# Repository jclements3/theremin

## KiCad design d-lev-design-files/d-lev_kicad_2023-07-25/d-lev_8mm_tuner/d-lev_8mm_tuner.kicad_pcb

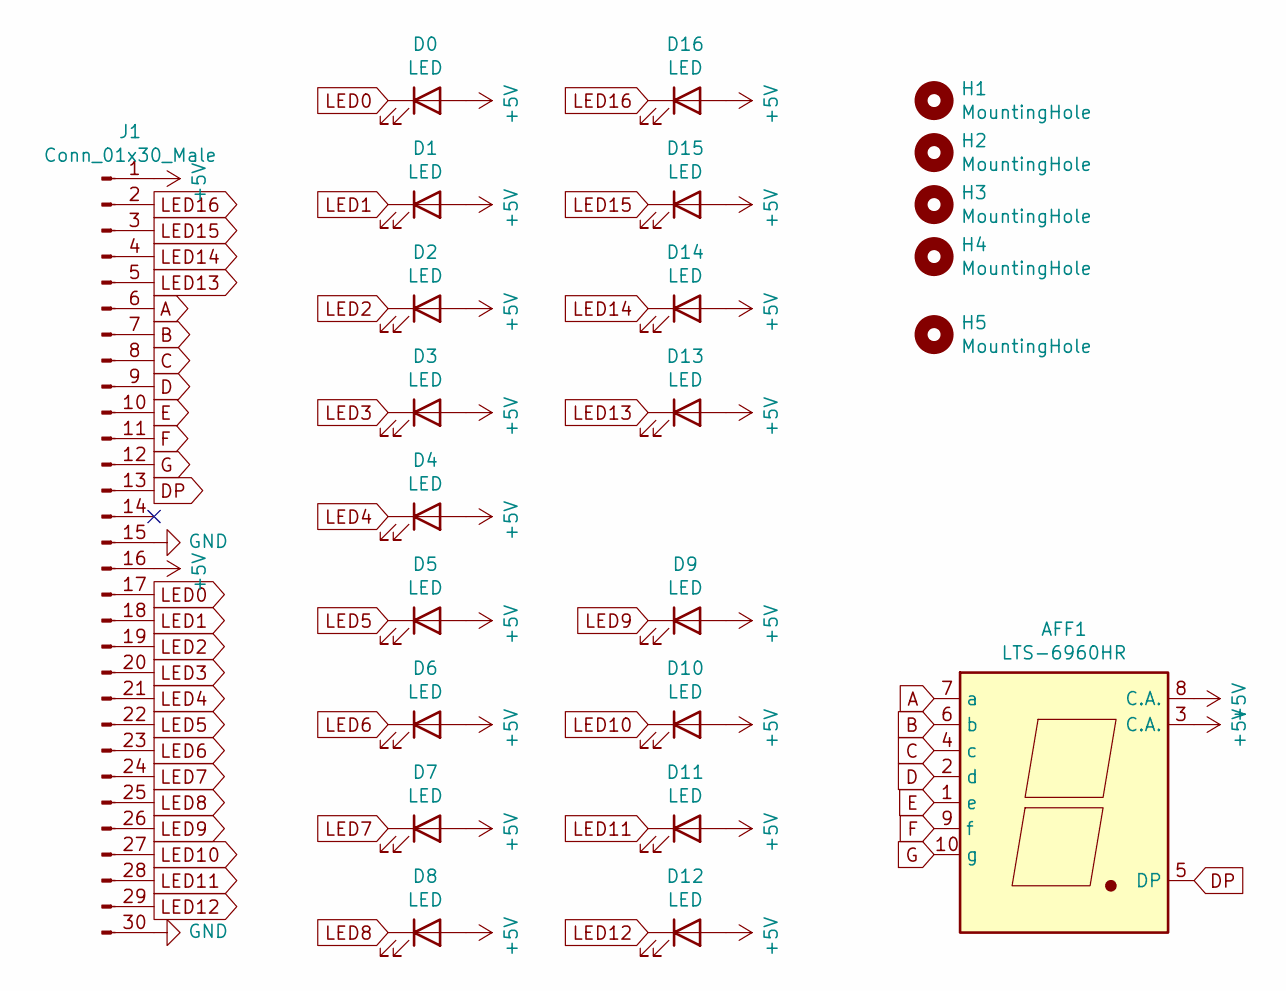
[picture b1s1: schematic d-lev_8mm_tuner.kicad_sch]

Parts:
AFF1: LTS-6960HR; 7-segment_half_inch
D0, D1, D2, D3, D4, D5, D6, D7, D8, D9, D10, D11, D12, D13, D14, D15, D16: LED; LED_D8.0mm
H1, H2, H3, H4: MountingHole; MountingHole_3.2mm_M3
H5: MountingHole; MountingHole_2.5mm_Pad_TopBottom
J1: Conn_01x30_Male; PinHeader_1x30_P2.54mm_Vertical

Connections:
+5V: AFF1.3 (C.A.), AFF1.8 (C.A.), D0.2 (A), D1.2 (A), D2.2 (A), D3.2 (A), D4.2 (A), D5.2 (A), D6.2 (A), D7.2 (A), D8.2 (A), D9.2 (A), D10.2 (A), D11.2 (A), D12.2 (A), D13.2 (A), D14.2 (A), D15.2 (A), D16.2 (A), J1.1, J1.16
A: AFF1.7 (a), J1.6
B: AFF1.6 (b), J1.7
C: AFF1.4 (c), J1.8
D: AFF1.2 (d), J1.9
DP: AFF1.5 (DP), J1.13
E: AFF1.1 (e), J1.10
F: AFF1.9 (f), J1.11
G: AFF1.10 (g), J1.12
GND: J1.15, J1.30
LED0: D0.1 (K), J1.17
LED1: D1.1 (K), J1.18
LED2: D2.1 (K), J1.19
LED3: D3.1 (K), J1.20
LED4: D4.1 (K), J1.21
LED5: D5.1 (K), J1.22
LED6: D6.1 (K), J1.23
LED7: D7.1 (K), J1.24
LED8: D8.1 (K), J1.25
LED9: D9.1 (K), J1.26
LED10: D10.1 (K), J1.27
LED11: D11.1 (K), J1.28
LED12: D12.1 (K), J1.29
LED13: D13.1 (K), J1.5
LED14: D14.1 (K), J1.4
LED15: D15.1 (K), J1.3
LED16: D16.1 (K), J1.2

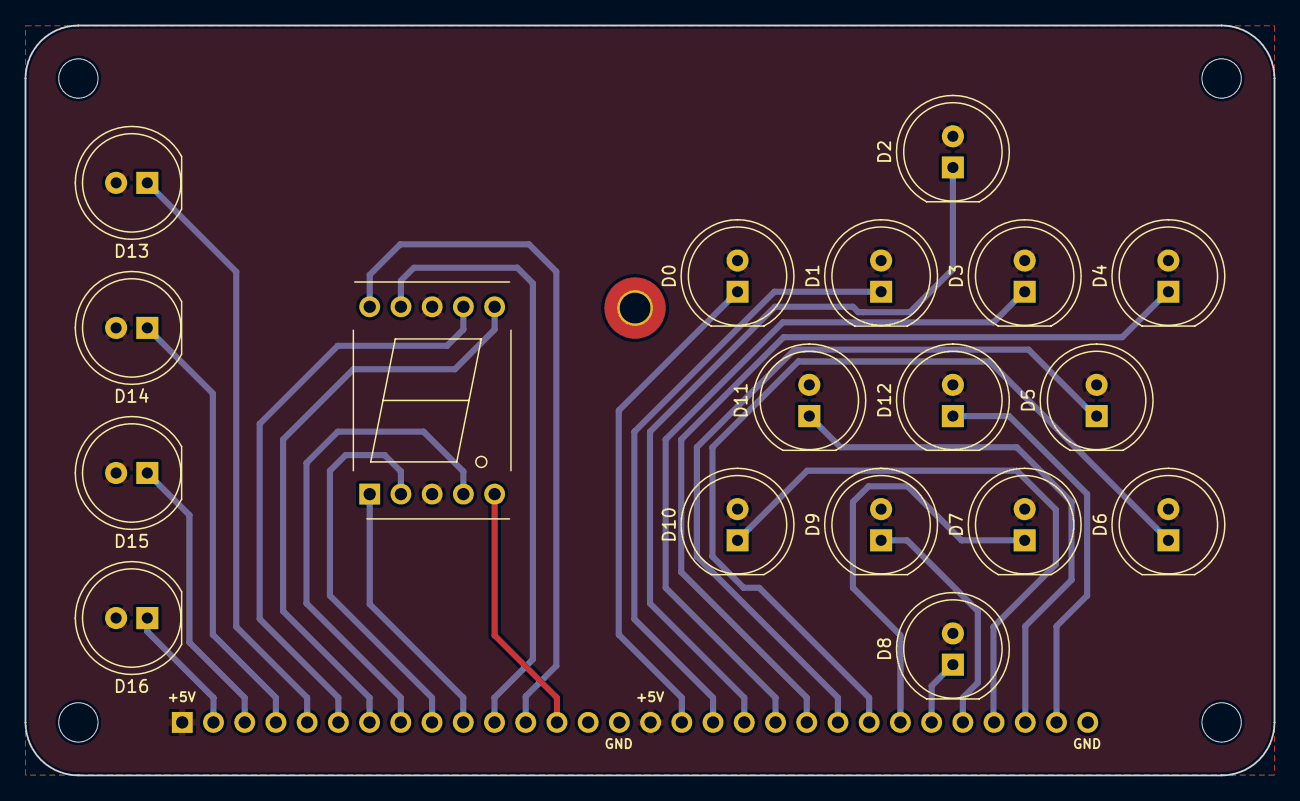
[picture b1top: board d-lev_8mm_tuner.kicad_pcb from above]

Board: 2 copper layers, 101.6 x 61.0 mm, 24 parts (1 on the bottom side), 27 nets.

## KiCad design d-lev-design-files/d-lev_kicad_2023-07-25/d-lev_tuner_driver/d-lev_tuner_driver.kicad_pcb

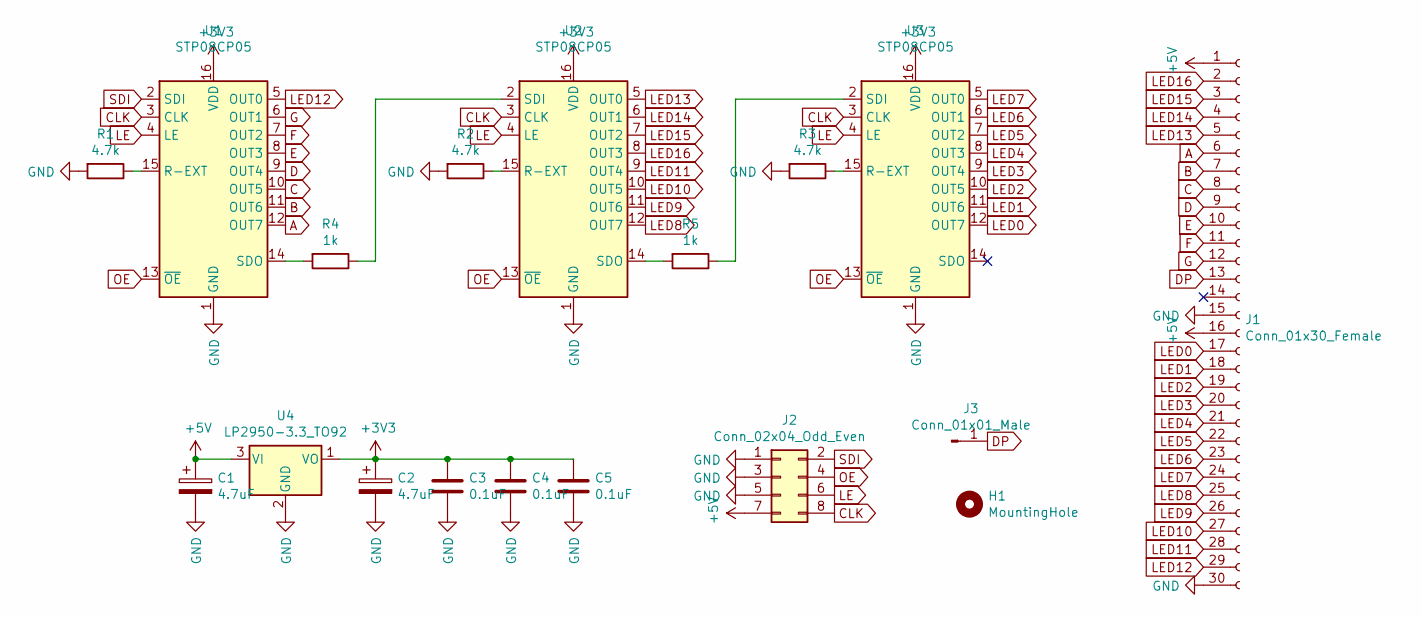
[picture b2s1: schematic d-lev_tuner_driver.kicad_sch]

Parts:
C1, C2: 4.7uF; CP_Radial_Tantal_D4.5mm_P2.50mm
C3, C4, C5: 0.1uF; C_Disc_D3.0mm_W2.0mm_P2.50mm
H1: MountingHole; MountingHole_3.2mm_M3
J1: Conn_01x30_Female; PinSocket_1x30_P2.54mm_Vertical
J2: Conn_02x04_Odd_Even; IDC-Header_2x04_P2.54mm_Vertical
J3: Conn_01x01_Male; PinHeader_1x01_P2.54mm_Vertical
R1, R2, R3: 4.7k; R_Axial_DIN0207_L6.3mm_D2.5mm_P5.08mm_Vertical
R4, R5: 1k; R_Axial_DIN0207_L6.3mm_D2.5mm_P5.08mm_Vertical
U1, U2, U3: STP08CP05; DIP-16_W7.62mm
U4: LP2950-3.3_TO92; TO-92_Inline_Wide

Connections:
+3V3: C2.1, C3.1, C4.1, C5.1, U1.16 (VDD), U2.16 (VDD), U3.16 (VDD), U4.1 (VO)
+5V: C1.1, J1.1, J1.16, J2.7, U4.3 (VI)
A: J1.6, U1.12 (OUT7)
B: J1.7, U1.11 (OUT6)
C: J1.8, U1.10 (OUT5)
CLK: J2.8, U1.3 (CLK), U2.3 (CLK), U3.3 (CLK)
D: J1.9, U1.9 (OUT4)
DP: J1.13, J3.1
E: J1.10, U1.8 (OUT3)
F: J1.11, U1.7 (OUT2)
G: J1.12, U1.6 (OUT1)
GND: C1.2, C2.2, C3.2, C4.2, C5.2, J1.15, J1.30, J2.1, J2.3, J2.5, R1.2, R2.2, R3.2, U1.1 (GND), U2.1 (GND), U3.1 (GND), U4.2 (GND)
LE: J2.6, U1.4 (LE), U2.4 (LE), U3.4 (LE)
LED0: J1.17, U3.12 (OUT7)
LED1: J1.18, U3.11 (OUT6)
LED2: J1.19, U3.10 (OUT5)
LED3: J1.20, U3.9 (OUT4)
LED4: J1.21, U3.8 (OUT3)
LED5: J1.22, U3.7 (OUT2)
LED6: J1.23, U3.6 (OUT1)
LED7: J1.24, U3.5 (OUT0)
LED8: J1.25, U2.12 (OUT7)
LED9: J1.26, U2.11 (OUT6)
LED10: J1.27, U2.10 (OUT5)
LED11: J1.28, U2.9 (OUT4)
LED12: J1.29, U1.5 (OUT0)
LED13: J1.5, U2.5 (OUT0)
LED14: J1.4, U2.6 (OUT1)
LED15: J1.3, U2.7 (OUT2)
LED16: J1.2, U2.8 (OUT3)
unnamed: R1.1, U1.15 (R-EXT)
unnamed: R2.1, U2.15 (R-EXT)
unnamed: R3.1, U3.15 (R-EXT)
unnamed: R4.1, U2.2 (SDI)
unnamed: R4.2, U1.14 (SDO)
unnamed: R5.1, U3.2 (SDI)
unnamed: R5.2, U2.14 (SDO)
OE: J2.4, U1.13 (~OE), U2.13 (~OE), U3.13 (~OE)
SDI: J2.2, U1.2 (SDI)

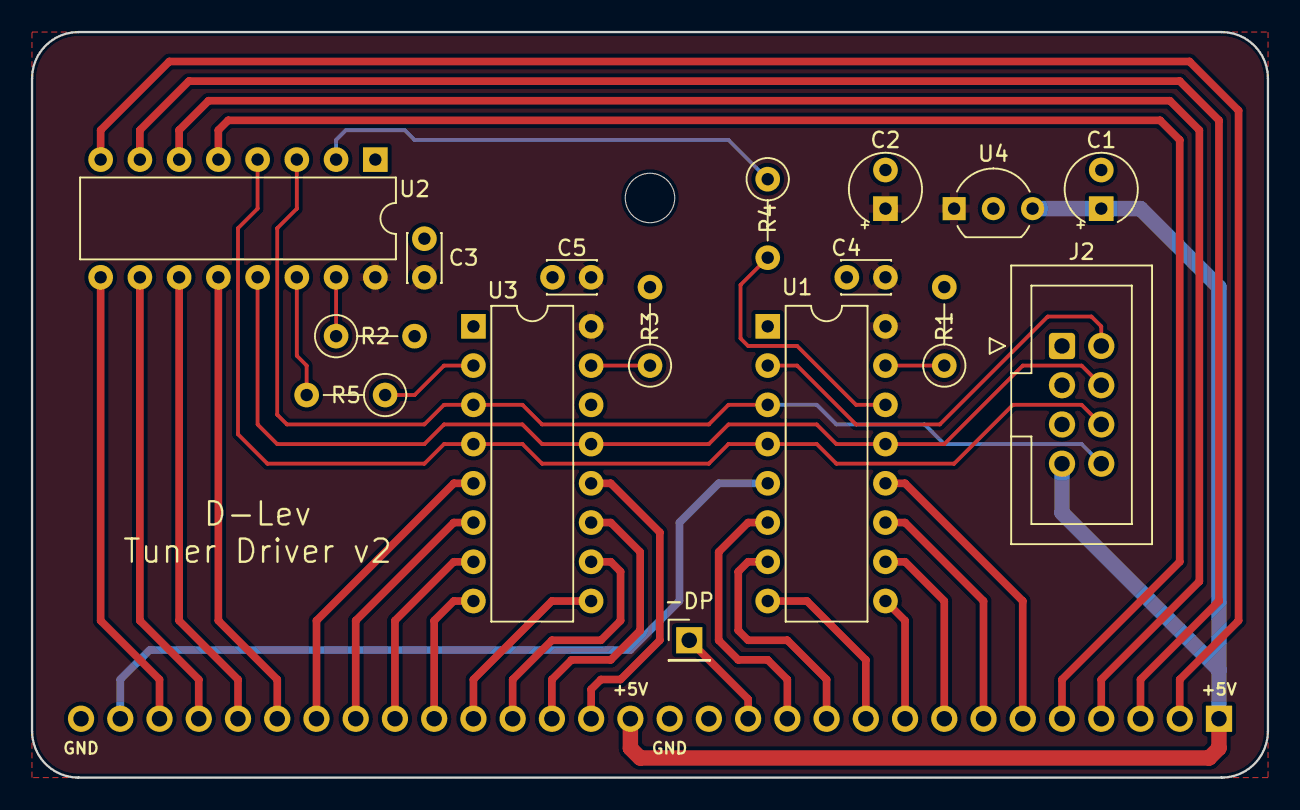
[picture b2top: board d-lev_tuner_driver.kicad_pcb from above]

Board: 2 copper layers, 80.0 x 48.3 mm, 18 parts (1 on the bottom side), 39 nets.

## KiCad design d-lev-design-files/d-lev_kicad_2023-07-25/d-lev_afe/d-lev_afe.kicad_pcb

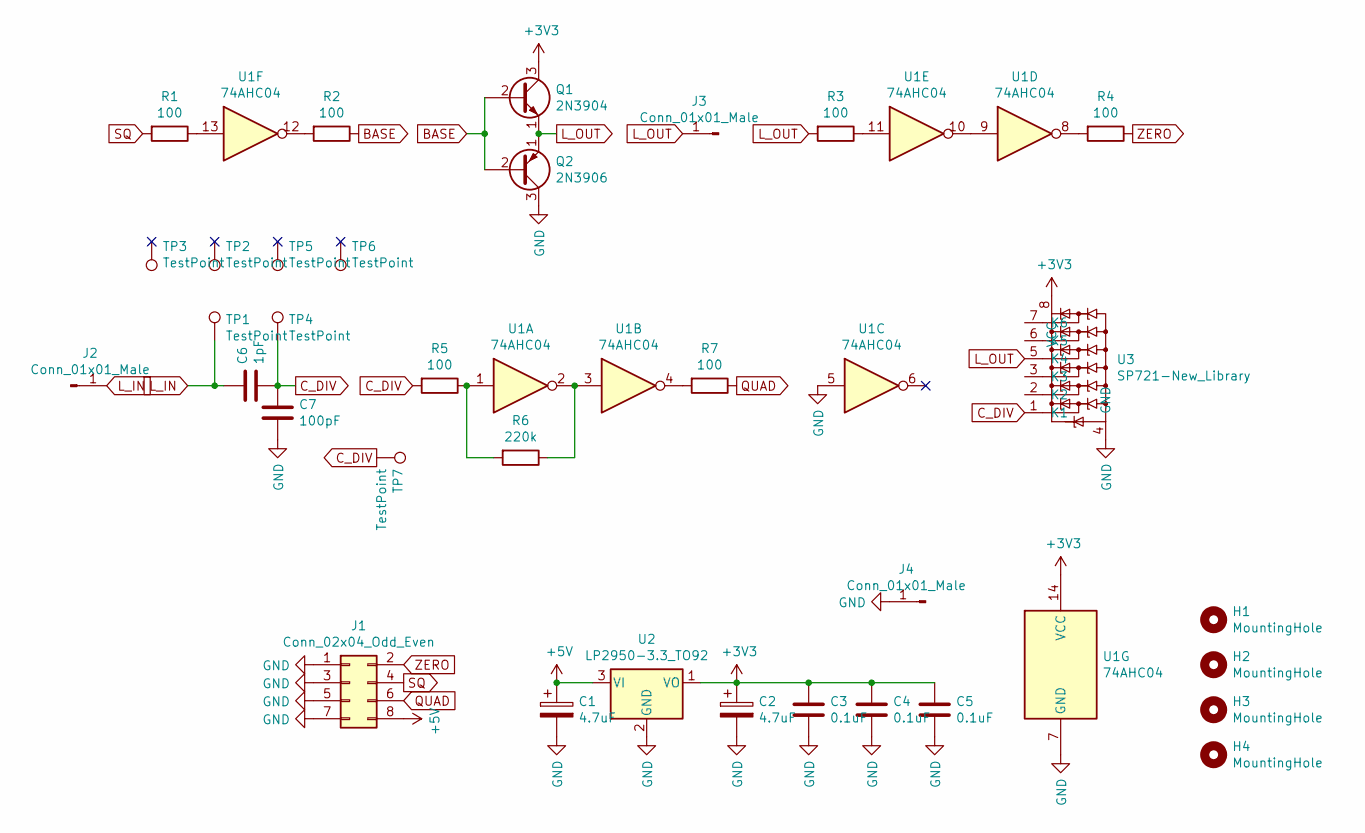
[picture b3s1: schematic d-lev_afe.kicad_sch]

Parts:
C1, C2: 4.7uF; CP_Radial_Tantal_D4.5mm_P2.50mm
C3, C4, C5: 0.1uF; C_Disc_D3.0mm_W2.0mm_P2.50mm
C6: 1pF; C_Disc_D4.3mm_W1.9mm_P5.00mm
C7: 100pF; C_Disc_D4.3mm_W1.9mm_P5.00mm
H1, H2, H3, H4: MountingHole; MountingHole_3.2mm_M3
J1: Conn_02x04_Odd_Even; IDC-Header_2x04_P2.54mm_Vertical
J2, J3, J4: Conn_01x01_Male; PinHeader_1x01_P2.54mm_Vertical
Q1: 2N3904; TO-92_Inline_Wide
Q2: 2N3906; TO-92_Inline_Wide
R1, R4, R7: 100; R_Axial_DIN0207_L6.3mm_D2.5mm_P10.16mm_Horizontal
R2, R3, R5: 100; R_Axial_DIN0207_L6.3mm_D2.5mm_P5.08mm_Vertical
R6: 220k; R_Axial_DIN0207_L6.3mm_D2.5mm_P5.08mm_Vertical
TP1, TP4: TestPoint; TestPoint_Pad_4.0x4.0mm
TP2, TP3, TP5, TP6: TestPoint; TestPoint_Pad_D3.0mm
TP7: TestPoint; PinHeader_1x01_P2.54mm_Vertical
U1: 74AHC04; DIP-14_W7.62mm_Socket
U2: LP2950-3.3_TO92; TO-92_Inline_Wide
U3: SP721-New_Library; DIP-8_W7.62mm_Socket

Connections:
+3V3: C2.1, C3.1, C4.1, C5.1, Q1.3 (C), U1.14 (VCC), U2.1 (VO), U3.8 (VCC)
+5V: C1.1, J1.8, U2.3 (VI)
BASE: Q1.2 (B), Q2.2 (B), R2.1
C_DIV: C6.2, C7.1, R5.2, TP4.1, TP7.1, U3.1 (K1)
GND: C1.2, C2.2, C3.2, C4.2, C5.2, C7.2, J1.1, J1.3, J1.5, J1.7, J4.1, Q2.3 (C), U1.5, U1.7 (GND), U2.2 (GND), U3.4 (GND)
L_IN: C6.1, J2.1, TP1.1
L_OUT: J3.1, Q1.1 (E), Q2.1 (E), R3.2, U3.5 (K4)
unnamed: R1.1, U1.13
unnamed: R2.2, U1.12
unnamed: R3.1, U1.11
unnamed: R4.2, U1.8
unnamed: R5.1, R6.2, U1.1
unnamed: R6.1, U1.2, U1.3
unnamed: R7.2, U1.4
unnamed: U1.9, U1.10
QUAD: J1.6, R7.1
SQ: J1.4, R1.2
ZERO: J1.2, R4.1

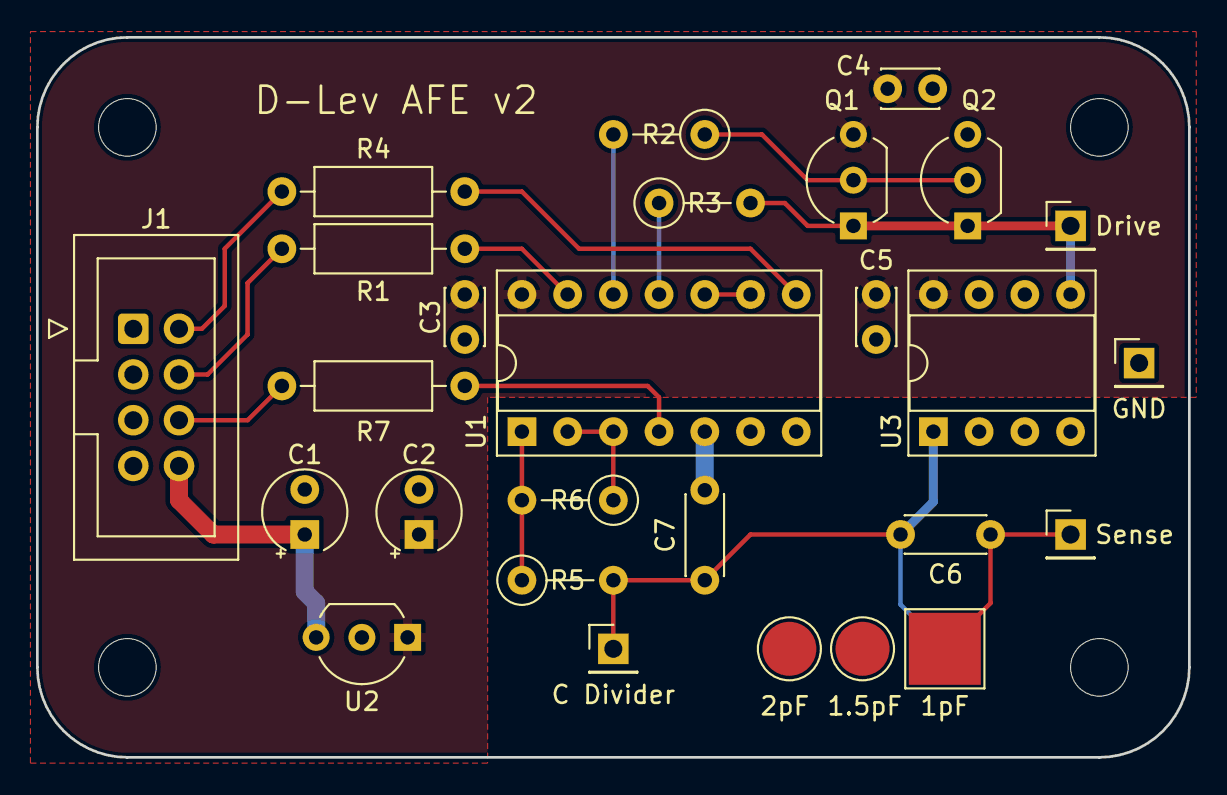
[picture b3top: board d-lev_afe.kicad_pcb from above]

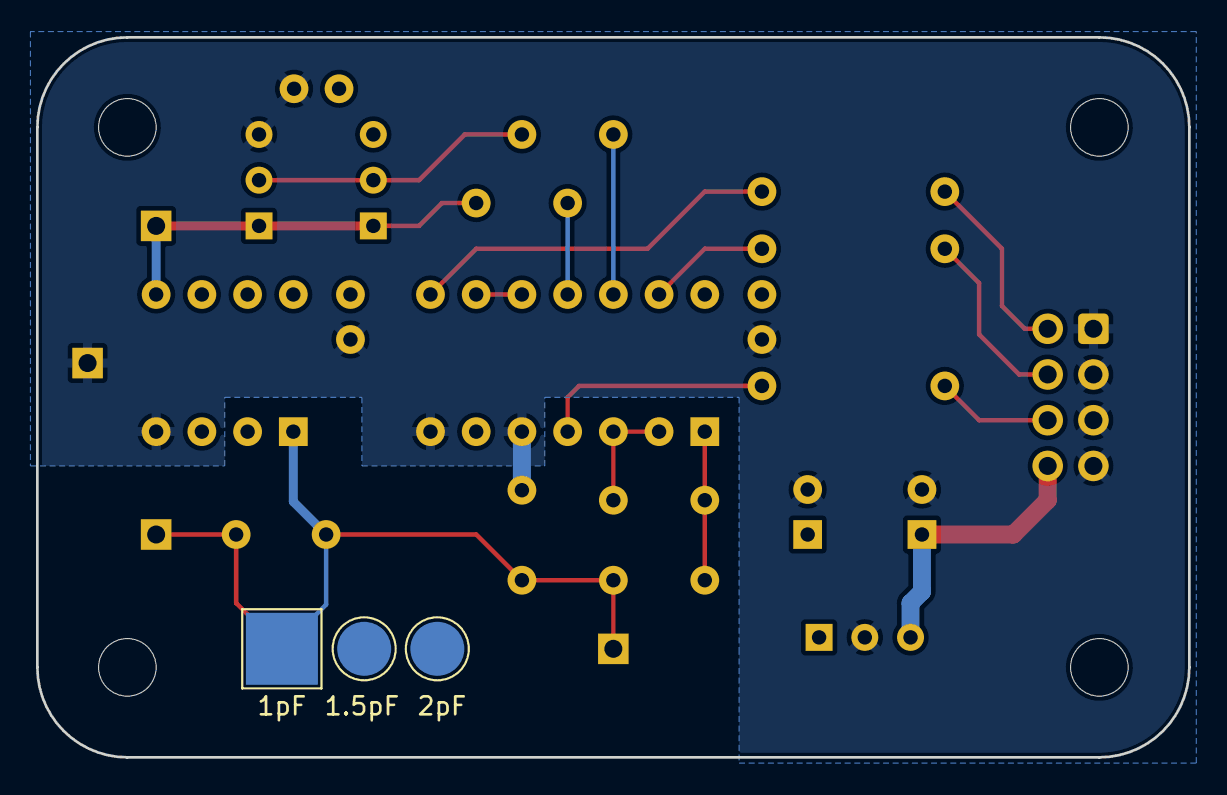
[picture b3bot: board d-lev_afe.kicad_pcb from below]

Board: 2 copper layers, 64.0 x 40.0 mm, 34 parts (3 on the bottom side), 18 nets.

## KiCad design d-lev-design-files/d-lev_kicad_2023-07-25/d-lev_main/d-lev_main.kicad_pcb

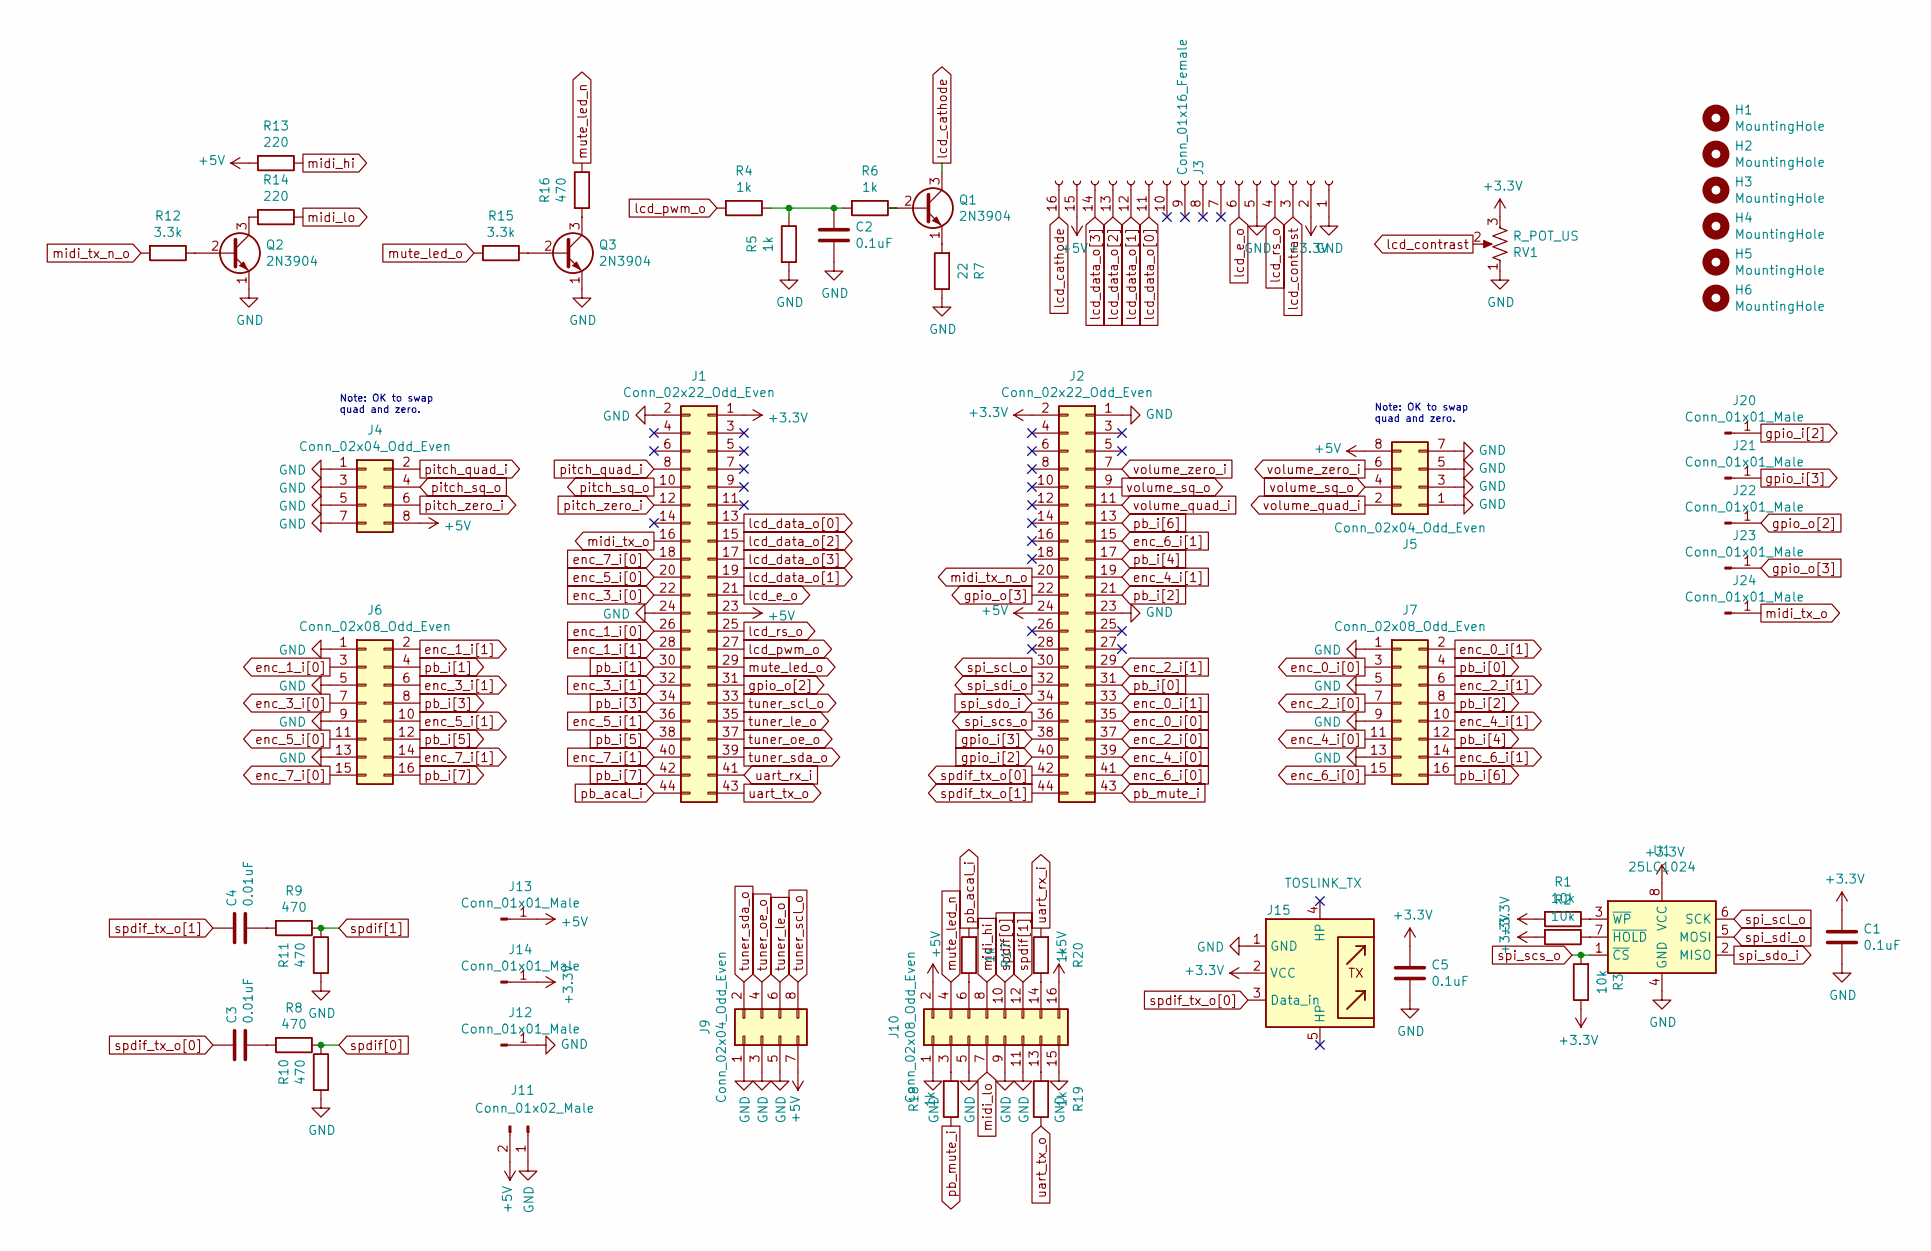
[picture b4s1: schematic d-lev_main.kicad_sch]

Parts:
C1, C5: 0.1uF; C_Disc_D3.0mm_W2.0mm_P2.50mm
C2: 0.1uF; C_Disc_D4.3mm_W1.9mm_P5.00mm
C3, C4: 0.01uF; C_Disc_D3.0mm_W2.0mm_P2.50mm
H1, H2, H3, H4, H5, H6: MountingHole; MountingHole_3.2mm_M3
J1, J2: Conn_02x22_Odd_Even; PinSocket_2x22_P2.54mm_Vertical
J3: Conn_01x16_Female; PinSocket_1x16_P2.54mm_Vertical
J4, J5, J9: Conn_02x04_Odd_Even; IDC-Header_2x04_P2.54mm_Vertical
J6, J7, J10: Conn_02x08_Odd_Even; IDC-Header_2x08_P2.54mm_Vertical
J11: Conn_01x02_Male; Molex_KK-396_A-41791-0002_1x02_P3.96mm_Vertical
J12, J13, J14, J20, J21, J22, J23, J24: Conn_01x01_Male; PinHeader_1x01_P2.54mm_Vertical
J15: TOSLINK_TX
Q1, Q2, Q3: 2N3904; TO-92_Inline_Wide
R1, R2, R3: 10k; R_Axial_DIN0207_L6.3mm_D2.5mm_P10.16mm_Horizontal
R4, R5, R6, R17, R18, R19, R20: 1k; R_Axial_DIN0207_L6.3mm_D2.5mm_P10.16mm_Horizontal
R7: 22; R_Axial_DIN0207_L6.3mm_D2.5mm_P10.16mm_Horizontal
R8, R9, R10, R11, R16: 470; R_Axial_DIN0207_L6.3mm_D2.5mm_P10.16mm_Horizontal
R12, R15: 3.3k; R_Axial_DIN0207_L6.3mm_D2.5mm_P10.16mm_Horizontal
R13, R14: 220; R_Axial_DIN0207_L6.3mm_D2.5mm_P10.16mm_Horizontal
RV1: R_POT_US; Potentiometer_Runtron_RM-065_Vertical
U1: 25LC1024; DIP-8_W7.62mm_Socket

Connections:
+3V3: C1.1, C5.1, J1.1, J2.2, J3.2, J14.1, J15.2 (VCC), R1.2, R2.2, R3.1, RV1.3, U1.8 (VCC)
+5V: J1.23, J2.24, J3.15, J4.8, J5.8, J9.7, J10.2, J10.16, J11.2, J13.1, R13.2
GND: C1.2, C2.2, C5.2, J1.2, J1.24, J2.1, J2.23, J3.1, J3.5, J4.1, J4.3, J4.5, J4.7, J5.1, J5.3, J5.5, J5.7, J6.1, J6.5, J6.9, J6.13, J7.1, J7.5, J7.9, J7.13, J9.1, J9.3, J9.5, J10.1, J10.5, J10.9, J10.11, J10.15, J11.1, J12.1, J15.1 (GND), Q2.1 (E), Q3.1 (E), R5.2, R7.1, R10.2, R11.2, RV1.1, U1.4 (GND)
unnamed: C2.1, R4.1, R5.1, R6.2
unnamed: C3.2, R8.2
unnamed: C4.2, R9.2
unnamed: J10.3, R18.2
unnamed: J10.6, R17.1
unnamed: J10.13, R19.2
unnamed: J10.14, R20.1
unnamed: Q1.1 (E), R7.2
unnamed: Q1.2 (B), R6.1
unnamed: Q2.2 (B), R12.1
unnamed: Q2.3 (C), R14.2
unnamed: Q3.2 (B), R15.1
unnamed: Q3.3 (C), R16.2
unnamed: R1.1, U1.3 (~WP)
unnamed: R2.1, U1.7 (~HOLD)
enc_0_i[0]: J2.35, J7.3
enc_0_i[1]: J2.33, J7.2
enc_1_i[0]: J1.26, J6.3
enc_1_i[1]: J1.28, J6.2
enc_2_i[0]: J2.37, J7.7
enc_2_i[1]: J2.29, J7.6
enc_3_i[0]: J1.22, J6.7
enc_3_i[1]: J1.32, J6.6
enc_4_i[0]: J2.39, J7.11
enc_4_i[1]: J2.19, J7.10
enc_5_i[0]: J1.20, J6.11
enc_5_i[1]: J1.36, J6.10
enc_6_i[0]: J2.41, J7.15
enc_6_i[1]: J2.15, J7.14
enc_7_i[0]: J1.18, J6.15
enc_7_i[1]: J1.40, J6.14
gpio_i[2]: J2.40, J20.1
gpio_i[3]: J2.38, J21.1
gpio_o[2]: J1.31, J22.1
gpio_o[3]: J2.22, J23.1
lcd_cathode: J3.16, Q1.3 (C)
lcd_contrast: J3.3, RV1.2
lcd_data_o[0]: J1.13, J3.11
lcd_data_o[1]: J1.19, J3.12
lcd_data_o[2]: J1.15, J3.13
lcd_data_o[3]: J1.17, J3.14
lcd_e_o: J1.21, J3.6
lcd_pwm_o: J1.27, R4.2
lcd_rs_o: J1.25, J3.4
midi_hi: J10.8, R13.1
midi_lo: J10.7, R14.1
midi_tx_n_o: J2.20, R12.2
midi_tx_o: J1.16, J24.1
mute_led_n: J10.4, R16.1
mute_led_o: J1.29, R15.2
pb_acal_i: J1.44, R17.2
pb_i[0]: J2.31, J7.4
pb_i[1]: J1.30, J6.4
pb_i[2]: J2.21, J7.8
pb_i[3]: J1.34, J6.8
pb_i[4]: J2.17, J7.12
pb_i[5]: J1.38, J6.12
pb_i[6]: J2.13, J7.16
pb_i[7]: J1.42, J6.16
pb_mute_i: J2.43, R18.1
pitch_quad_i: J1.8, J4.2
pitch_sq_o: J1.10, J4.4
pitch_zero_i: J1.12, J4.6
spdif[0]: J10.10, R8.1, R10.1
spdif[1]: J10.12, R9.1, R11.1
spdif_tx_o[0]: C3.1, J2.42, J15.3 (Data_in)
spdif_tx_o[1]: C4.1, J2.44
spi_scl_o: J2.30, U1.6 (SCK)
spi_scs_o: J2.36, R3.2, U1.1 (~CS)
spi_sdi_o: J2.32, U1.5 (MOSI)
spi_sdo_i: J2.34, U1.2 (MISO)
tuner_le_o: J1.35, J9.6
tuner_oe_o: J1.37, J9.4
tuner_scl_o: J1.33, J9.8
tuner_sda_o: J1.39, J9.2
uart_rx_i: J1.41, R20.2
uart_tx_o: J1.43, R19.1
volume_quad_i: J2.11, J5.2
volume_sq_o: J2.9, J5.4
volume_zero_i: J2.7, J5.6

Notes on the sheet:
Note: OK to swap quad and zero.

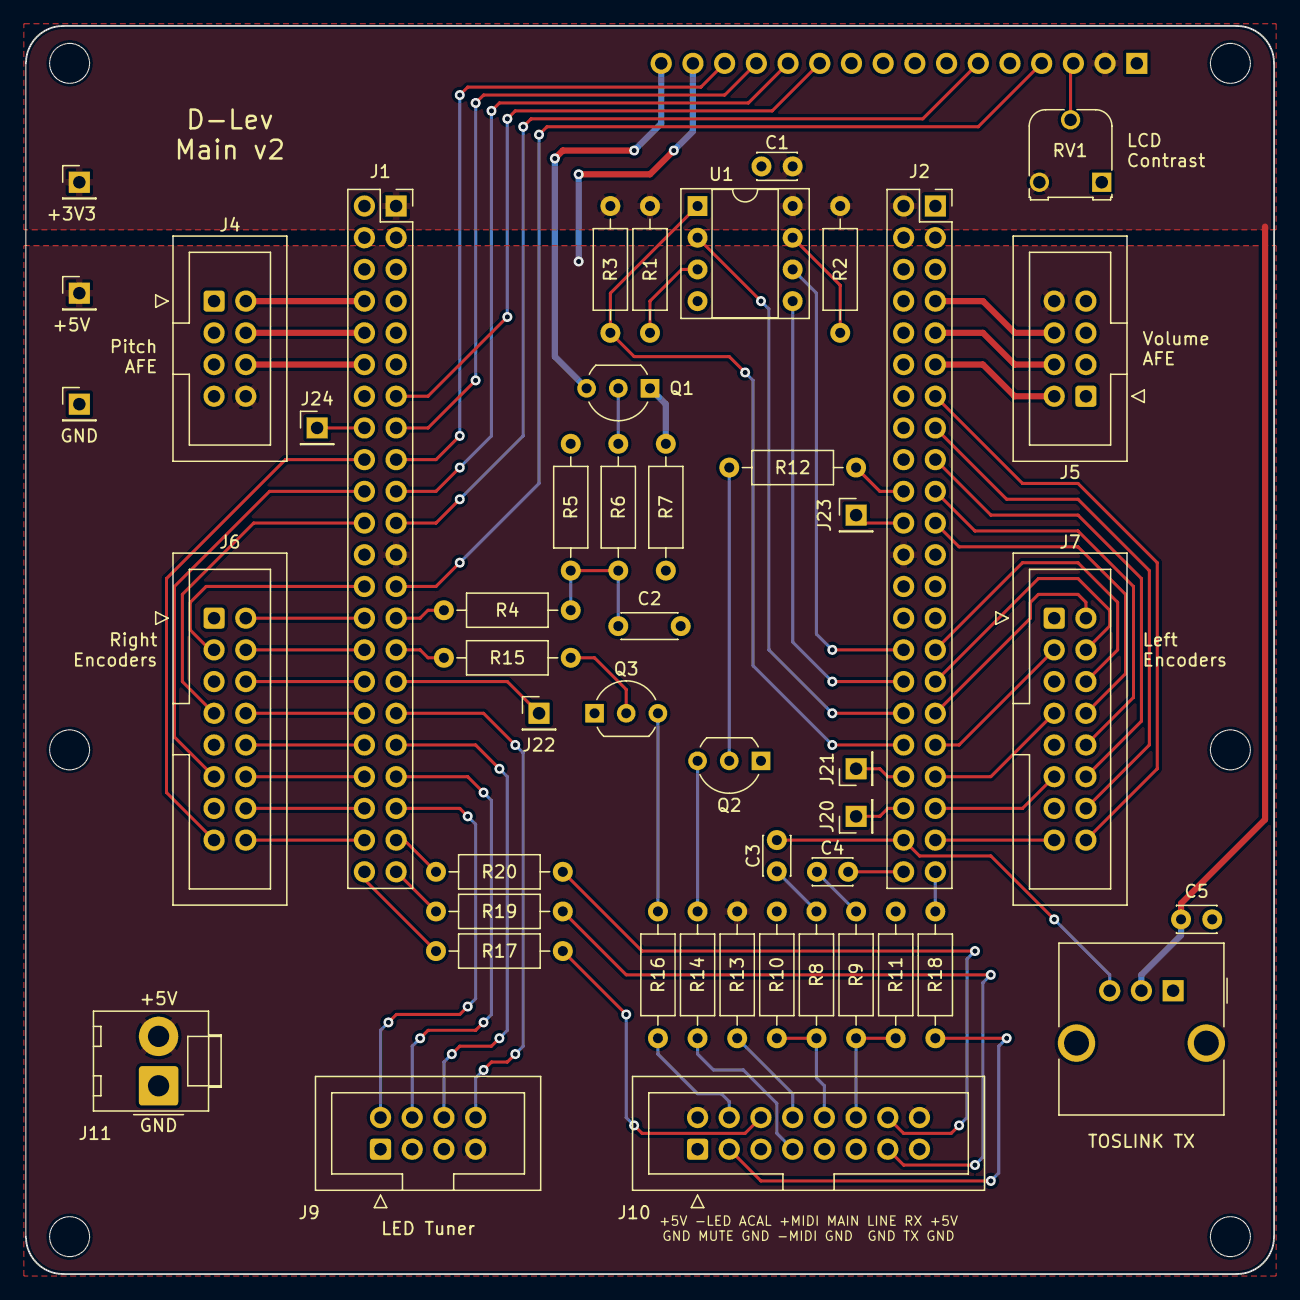
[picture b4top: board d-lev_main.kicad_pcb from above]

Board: 2 copper layers, 100.0 x 100.0 mm, 55 parts (1 on the bottom side), 83 nets.

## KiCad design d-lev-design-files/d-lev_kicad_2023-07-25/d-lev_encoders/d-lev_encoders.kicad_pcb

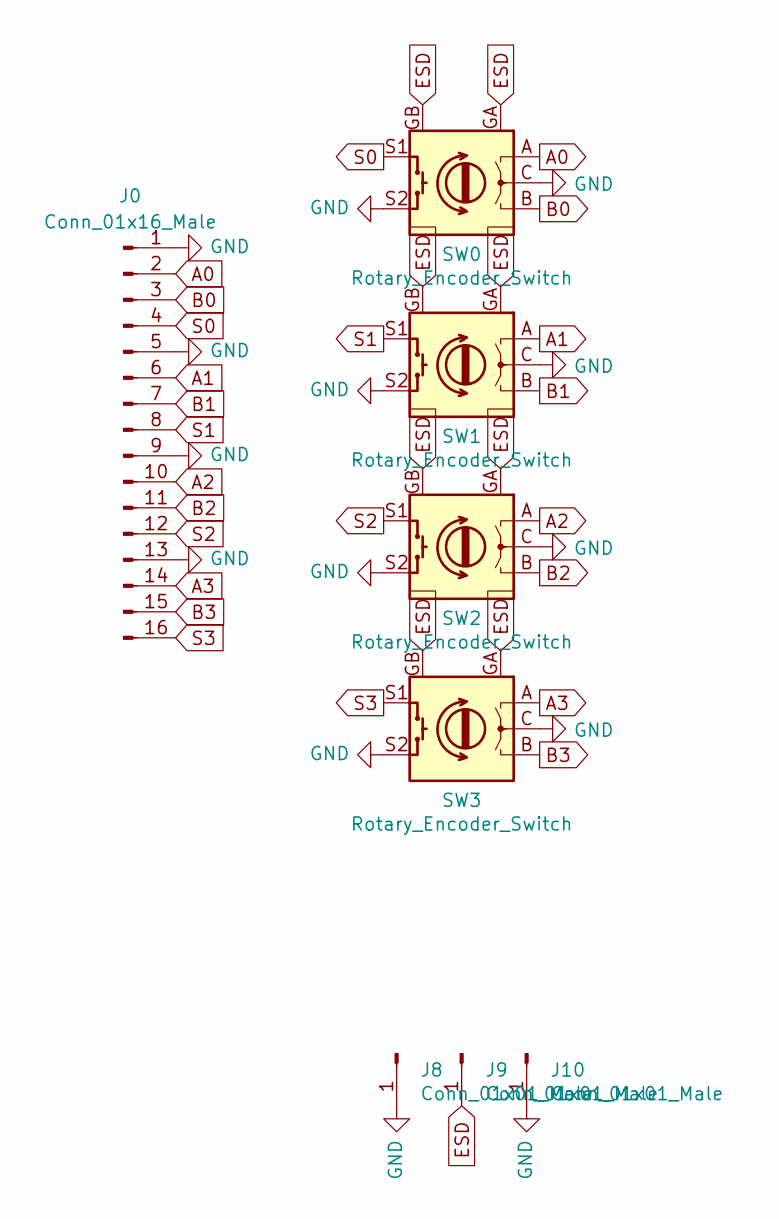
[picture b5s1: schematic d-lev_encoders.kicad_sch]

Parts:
J0: Conn_01x16_Male; Stagger_lee_2x8_P1.27mm
J8, J9, J10: Conn_01x01_Male; PinHeader_1x01_P2.54mm_Vertical
SW0, SW1, SW2, SW3: Rotary_Encoder_Switch; RotaryEncoder_Alps_EC11E-Switch_Vertical_H20mm_CircularMoun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

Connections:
A0: J0.2, SW0.A
A1: J0.6, SW1.A
A2: J0.10, SW2.A
A3: J0.14, SW3.A
B0: J0.3, SW0.B
B1: J0.7, SW1.B
B2: J0.11, SW2.B
B3: J0.15, SW3.B
ESD: J9.1, SW0.GA (GND), SW0.GB (GND), SW1.GA (GND), SW1.GB (GND), SW2.GA (GND), SW2.GB (GND), SW3.GA (GND), SW3.GB (GND)
GND: J0.1, J0.5, J0.9, J0.13, J8.1, J10.1, SW0.C, SW0.S2, SW1.C, SW1.S2, SW2.C, SW2.S2, SW3.C, SW3.S2
S0: J0.4, SW0.S1
S1: J0.8, SW1.S1
S2: J0.12, SW2.S1
S3: J0.16, SW3.S1

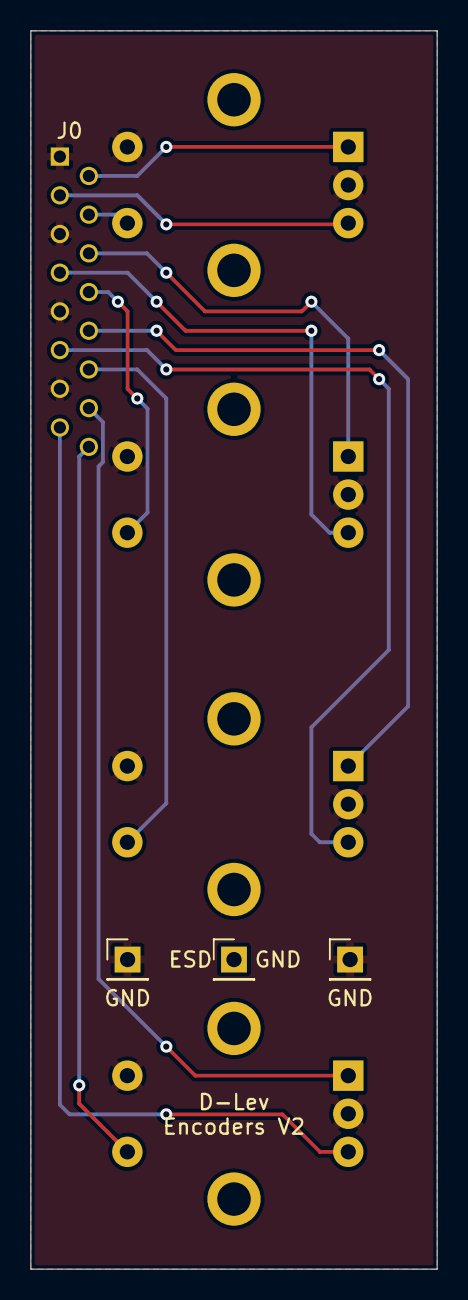
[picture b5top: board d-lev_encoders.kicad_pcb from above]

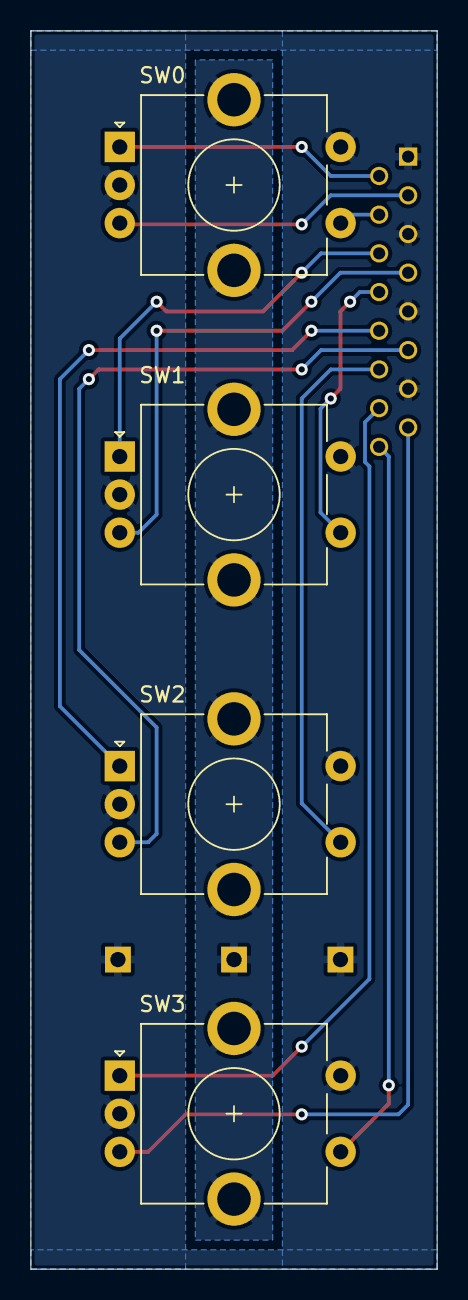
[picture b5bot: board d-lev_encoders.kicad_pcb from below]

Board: 2 copper layers, 26.7 x 81.3 mm, 8 parts (4 on the bottom side), 14 nets.
